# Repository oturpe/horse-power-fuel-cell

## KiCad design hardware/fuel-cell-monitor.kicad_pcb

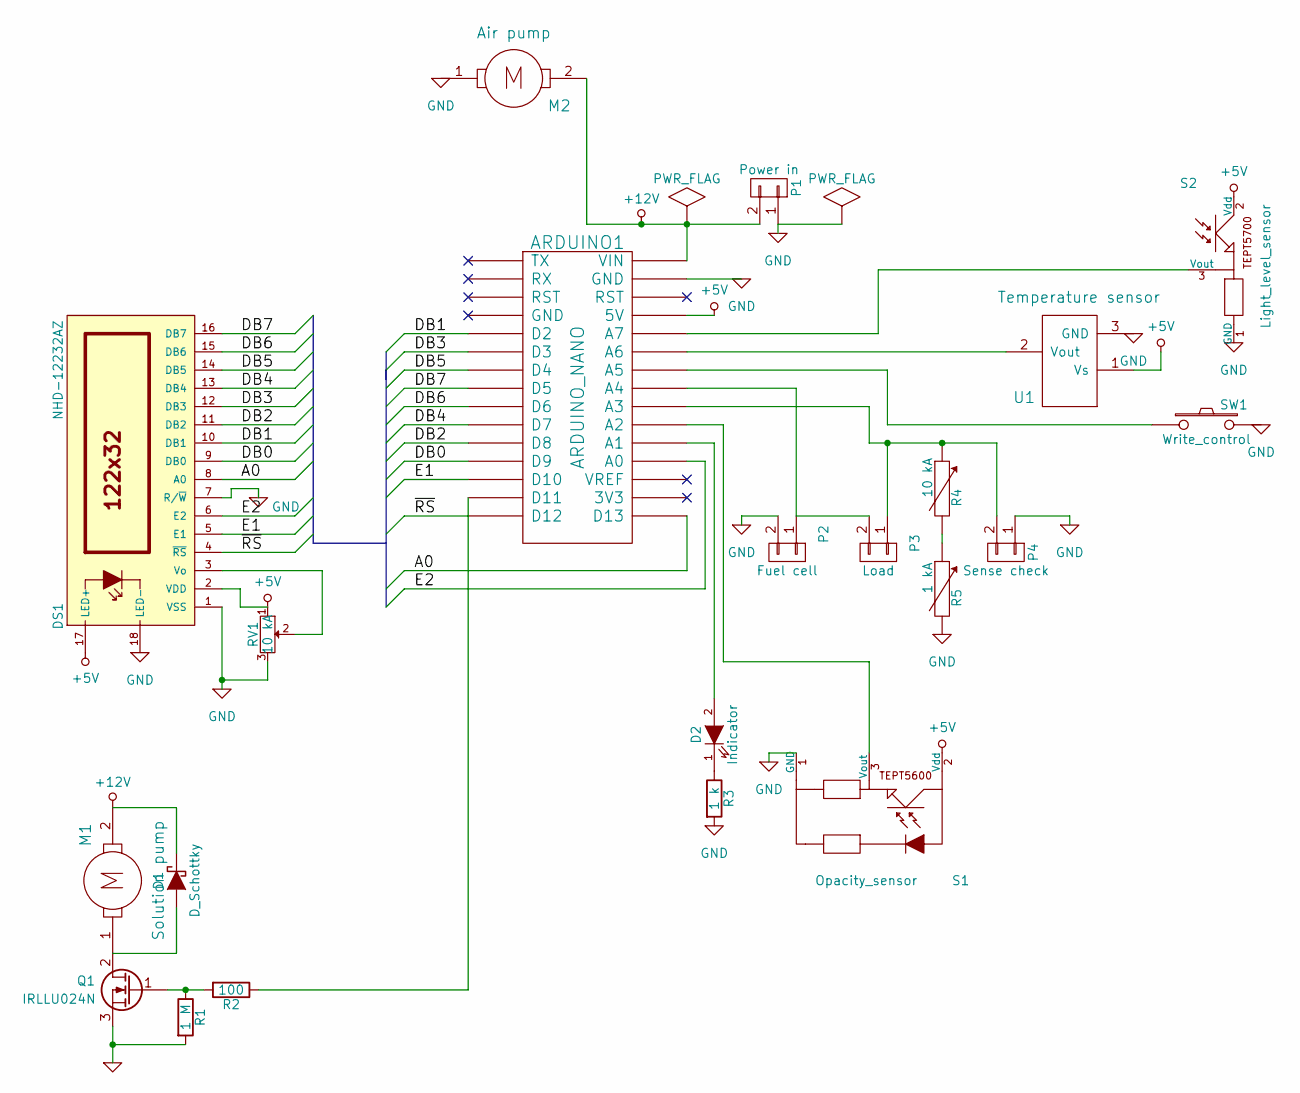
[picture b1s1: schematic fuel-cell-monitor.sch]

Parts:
ARDUINO1: ARDUINO_NANO; arduino_nano_header
D1: D_Schottky; Diode_DO-35_SOD27_Horizontal_RM10
D2: Indicator; LED-5MM
DS1: NHD-12232AZ; IDC_Header_Straight_20pins
M1: Solution pump; Big_green_chocolate_1x2
M2: Air pump; Big_green_chocolate_1x2
P1: Power in; Big_green_chocolate_1x2
P2: Fuel cell; Big_green_chocolate_1x2
P3: Load; Big_green_chocolate_1x2
P4: Sense check; PINHEAD1-2
Q1: IRLLU024N; TO-251AA
R1: 1 M; Resistor_Horizontal_RM10mm
R2: 100; Resistor_Horizontal_RM10mm
R3: 1 k; Resistor_Horizontal_RM10mm
R4: 10 kA; Trimmer_ACP_*V10
R5: 1 kA; Trimmer_ACP_*V10
RV1: 10 kA; Trimmer_ACP_*V10
S1: Opacity_sensor; Big_green_chocolate_1x3
S2: Light_level_sensor; Big_green_chocolate_1x3
SW1: Write_control; SW_PUSH_6mmx6mm
U1: Temperature sensor; Big_green_chocolate_1x3

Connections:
+5V: ARDUINO1.27 (5V), DS1.2 (VDD), DS1.17 (LED+), RV1.1, S1.2 (Vdd), S2.2 (Vdd), U1.1 (Vs)
+12V: ARDUINO1.30 (VIN), D1.1 (K), M1.2, M2.2, P1.2
/A0: ARDUINO1.16 (D13), DS1.8 (A0)
/DB0: ARDUINO1.12 (D9), DS1.9 (DB0)
/DB1: ARDUINO1.5 (D2), DS1.10 (DB1)
/DB2: ARDUINO1.11 (D8), DS1.11 (DB2)
/DB3: ARDUINO1.6 (D3), DS1.12 (DB3)
/DB4: ARDUINO1.10 (D7), DS1.13 (DB4)
/DB5: ARDUINO1.7 (D4), DS1.14 (DB5)
/DB6: ARDUINO1.9 (D6), DS1.15 (DB6)
/DB7: ARDUINO1.8 (D5), DS1.16 (DB7)
/E1: ARDUINO1.13 (D10), DS1.5 (E1)
/E2: ARDUINO1.19 (A0), DS1.6 (E2)
/~RS: ARDUINO1.15 (D12), DS1.4 (~RS)
GND: ARDUINO1.29 (GND), DS1.1 (VSS), DS1.7 (R/~W), DS1.18 (LED-), M2.1, P1.1, P2.2, P4.1, Q1.3 (S), R1.2, R3.2, R5.2, RV1.3, S1.1 (GND), S2.1 (GND), SW1.2, U1.3 (GND)
unnamed: ARDUINO1.14 (D11), R2.1
unnamed: ARDUINO1.20 (A1), D2.2 (A)
unnamed: ARDUINO1.21 (A2), S1.3 (Vout)
unnamed: ARDUINO1.22 (A3), P3.1, P4.2, R4.1
unnamed: ARDUINO1.23 (A4), P2.1, P3.2
unnamed: ARDUINO1.24 (A5), SW1.1
unnamed: ARDUINO1.25 (A6), U1.2 (Vout)
unnamed: ARDUINO1.26 (A7), S2.3 (Vout)
unnamed: D1.2 (A), M1.1, Q1.2 (D)
unnamed: D2.1 (K), R3.1
unnamed: DS1.3 (Vo), RV1.2
unnamed: Q1.1 (G), R1.1, R2.2
unnamed: R4.2, R5.1

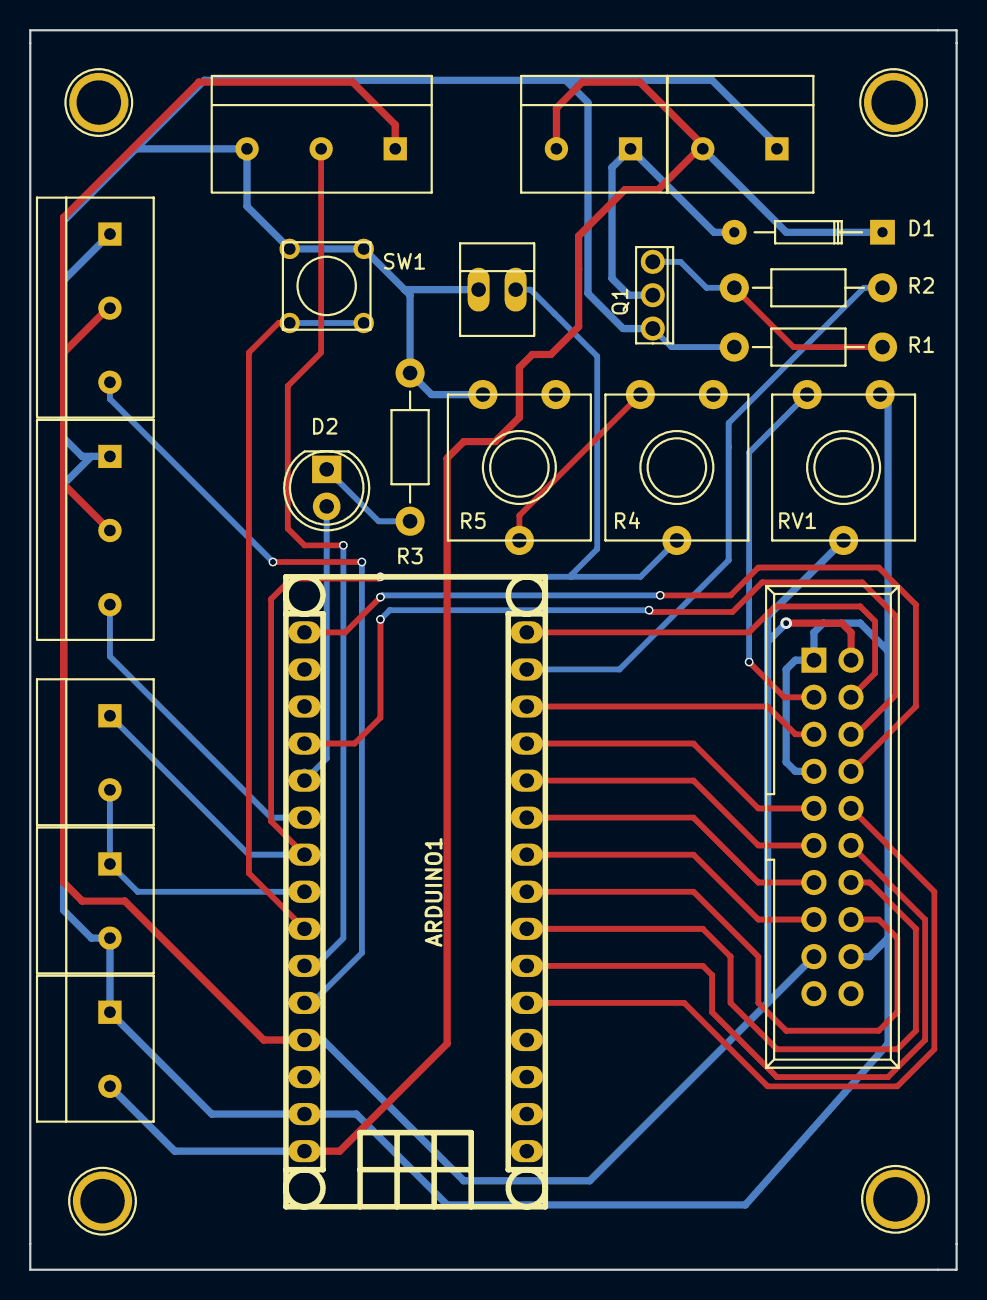
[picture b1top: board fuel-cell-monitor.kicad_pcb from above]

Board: 2 copper layers, 63.5 x 85.0 mm, 21 parts (0 on the bottom side), 28 nets.

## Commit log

2016-11-16 First version
    Starts recording, stops recording and outputs readings already.
    Some small problems remain.
2016-11-16 Remove todos, they were moved to other file
2016-11-17 Upgraded version
2016-11-20 Move measurement configuration to separate files
2016-11-22 Add multiple things to schematic
2016-11-23 Add missing parts to schematics
2016-11-23 Add recording of light levels
2016-11-23 Use whole dac range for voltage and ambient light measurement
2016-11-24 Add .gitignore ignoring kicad temporary files
2016-11-24 Fix problems found with KiCad electrical rules check
2016-11-28 Add code for opacity sensor + fix bug with output block number printout
2016-11-28 Fix remaining small things with the printed circuit board
    This included making the default trace 0.40 mm wide just be sure
    and fixing trimmer and potetiometer footprints.
2016-11-28 Fix potentiometer and trimmer footprint
2016-11-29 Add solution pump control code
2016-11-29 Final fixes before ordering pcbs.
    Most notably solution pump driver mosfet had to be changed. The earlier
    specified type did not work.
2016-12-12 Fix pins to match pcb, and add temperature sensor code
2016-12-14 Add more pcb problems
2016-12-14 Implement writing into the whole display screen
    However, no sensible information is written yet
2016-12-15 Implement printing of values in the screen
2016-12-16 Add forgotten screen files, plus change to show screen as flipped
2016-12-16 Coarse calibration of ambient light sensor
2016-12-16 Shorten solution pump on time
2017-01-03 Fix mean and transient recording intervals
    They are now one hour and one second, respectively
